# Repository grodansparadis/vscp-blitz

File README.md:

# Blitz
Wifi + Ethernet + CAN board for VSCP

<hr>

This project is part of the <a href="http://www.vscp.org">VSCP (Very Simple Control Protocol) project</a>. 

<hr>

This project is licensed under the 
<a href="http://creativecommons.org/licenses/by-nc-sa/3.0/">Creative Commons open source license Attribution-NonCommercial-ShareAlike 3.0 Unported</a>. 
Other license options are available by conacting <a href="malto:info@grodansparadis.com">Paradis of the Frog AB</a>

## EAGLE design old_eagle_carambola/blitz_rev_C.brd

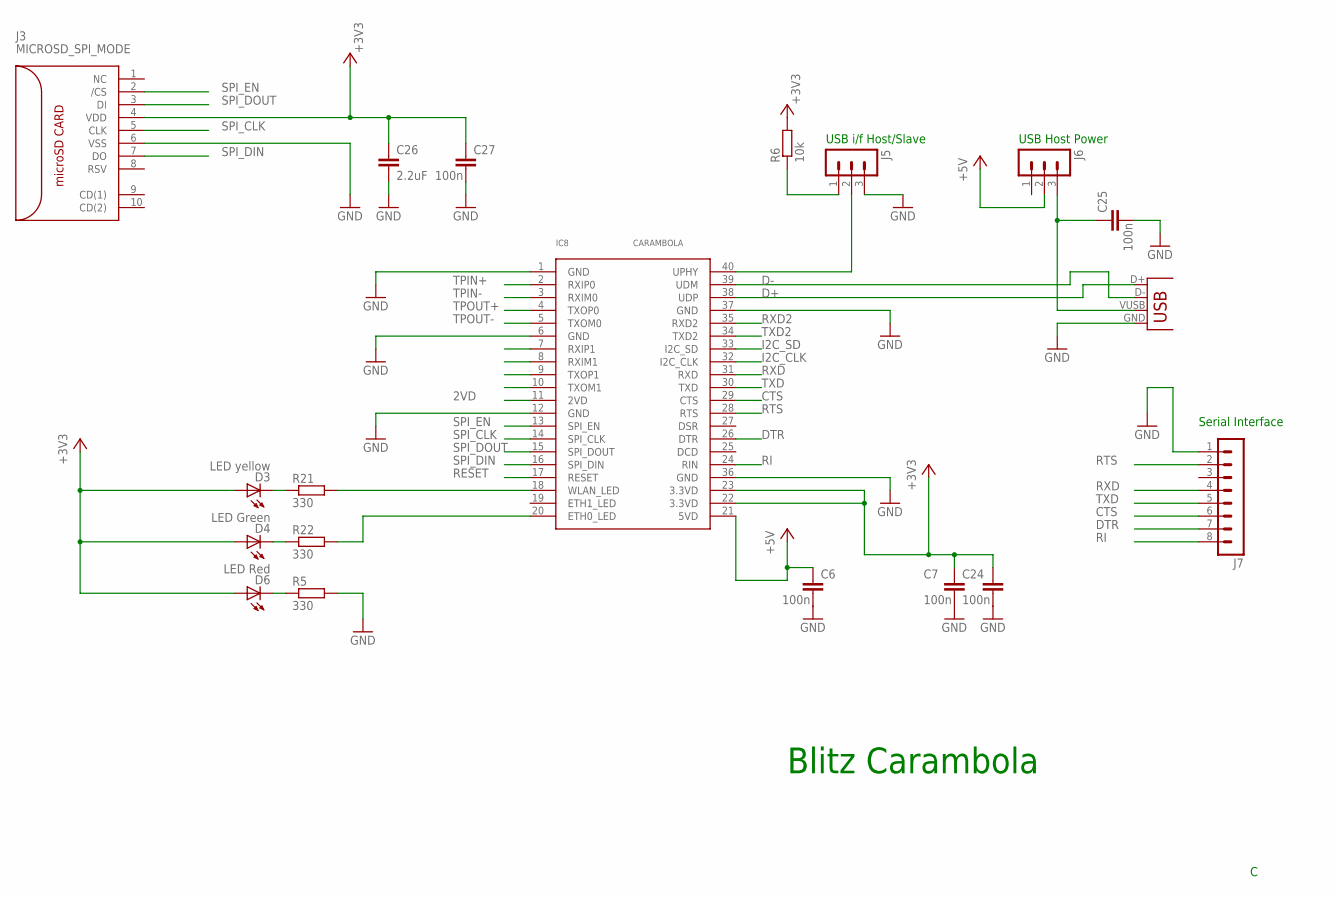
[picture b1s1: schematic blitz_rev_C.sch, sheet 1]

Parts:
C6, C7, C24, C25, C27: 100n; C0805
C26: 2.2uF; C2012
D3: LED yellow; C2012
D4: LED Green; C2012
D6: LED Red; C2012
IC8: CARAMBOLA
J3: MICROSD_SPI_MODE; MICRO_SD_CONNECTOR
J4: USB-B-S; USB-B-SMT
J5, J6: MA03-1
J7: MA08-1
R5, R21, R22: 330; M0805
R6: 10k; M0805

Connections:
2VD: IC8.11 (2VD)
+3V3: C7.1, C24.1, C26.1, C27.1, D3.1 (A), D4.1 (A), D6.1 (A), IC8.22 (3.3VD), IC8.23 (3.3VD), J3.4 (VDD), R6.2; also elsewhere on the board
+5V: C6.1, IC8.21 (5VD), J6.2; also elsewhere on the board
CTS: IC8.29 (CTS), J7.6
D+: IC8.38 (UDP), J4.D+
D-: IC8.39 (UDM), J4.D-
DTR: IC8.26 (DTR), J7.7
GND: C6.2, C7.2, C24.2, C25.2, C26.2, C27.2, IC8.1 (GND), IC8.6 (GND), IC8.12 (GND), IC8.36 (GND), IC8.37 (GND), J3.6 (VSS), J4.GND, J5.3, J7.1, R5.2; also elsewhere on the board
I2C_CLK: IC8.32 (I2C_CLK)
I2C_SD: IC8.33 (I2C_SD)
unnamed: J5.1, R6.1
unnamed: C25.1, J4.VUSB (VBUS), J6.3
unnamed: D4.2 (C), R22.1
unnamed: D3.2 (C), R21.1
unnamed: IC8.18 (WLAN_LED), R21.2
unnamed: IC8.20 (ETH0_LED), R22.2
unnamed: D6.2 (C), R5.1
unnamed: IC8.40 (UPHY), J5.2
RESET: IC8.17 (RESET)
RI: IC8.24 (RIN), J7.8
RTS: IC8.28 (RTS), J7.2
RXD: IC8.31 (RXD), J7.4
RXD2: IC8.35 (RXD2); also elsewhere on the board
SPI_CLK: IC8.14 (SPI_CLK), J3.5 (CLK)
SPI_DIN: IC8.16 (SPI_DIN), J3.7 (DO)
SPI_DOUT: IC8.15 (SPI_DOUT), J3.3 (DI)
SPI_EN: IC8.13 (SPI_EN), J3.2 (/CS)
TPIN+: IC8.2 (RXIP0); also elsewhere on the board
TPIN-: IC8.3 (RXIM0); also elsewhere on the board
TPOUT+: IC8.4 (TXOP0); also elsewhere on the board
TPOUT-: IC8.5 (TXOM0); also elsewhere on the board
TXD: IC8.30 (TXD), J7.5
TXD2: IC8.34 (TXD2); also elsewhere on the board

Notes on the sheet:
Blitz Carambola
USB i/f Host/Slave
USB Host Power
Serial Interface

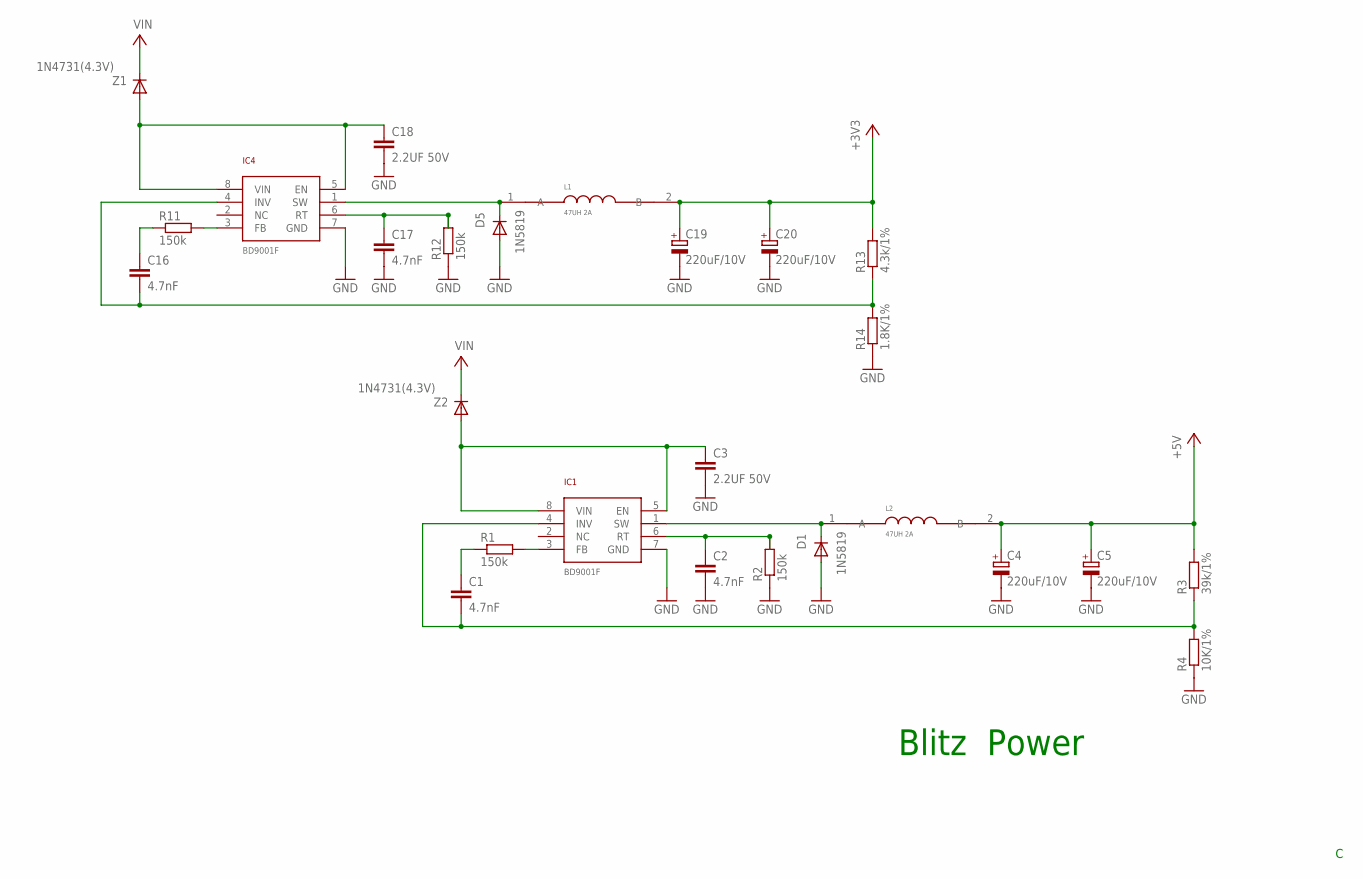
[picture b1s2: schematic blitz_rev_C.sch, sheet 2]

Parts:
C1, C2, C16, C17: 4.7nF; C0805
C3, C18: 2.2UF 50V; C2012
C4, C5, C19, C20: 220uF/10V; SMC_C
D1, D5: 1N5819; SOD-123
IC1, IC4: BD9001F; SOP8
L1, L2: 47UH 2A; NR10050T470M
R1, R2, R11, R12: 150k; M0805
R3: 39k/1%; M0805
R4: 10K/1%; M0805
R13: 4.3k/1%; M0805
R14: 1.8K/1%; M0805
Z1, Z2: 1N4731(4.3V); 1N4731

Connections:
+3V3: C19.+, C20.+, L1.2 (B), R13.2; also elsewhere on the board
+5V: C4.+, C5.+, L2.2 (B), R3.2; also elsewhere on the board
GND: C2.2, C3.2, C4.-, C5.-, C17.2, C18.2, C19.-, C20.-, D1.A, D5.A, IC1.7 (GND), IC4.7 (GND), R2.1, R4.1, R12.1, R14.1; also elsewhere on the board
unnamed: IC1.3 (FB), R1.2
unnamed: C1.1, R1.1
unnamed: C1.2, IC1.4 (INV), R3.1, R4.2
unnamed: C2.1, IC1.6 (RT), R2.2
unnamed: C3.1, IC1.5 (EN), IC1.8 (VIN), Z2.A
unnamed: D1.C, IC1.1 (SW), L2.1 (A)
unnamed: IC4.3 (FB), R11.2
unnamed: C16.1, R11.1
unnamed: C16.2, IC4.4 (INV), R13.1, R14.2
unnamed: C17.1, IC4.6 (RT), R12.2
unnamed: C18.1, IC4.5 (EN), IC4.8 (VIN), Z1.A
unnamed: D5.C, IC4.1 (SW), L1.1 (A)
V+: Z1.C, Z2.C; also elsewhere on the board

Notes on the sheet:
Blitz Power

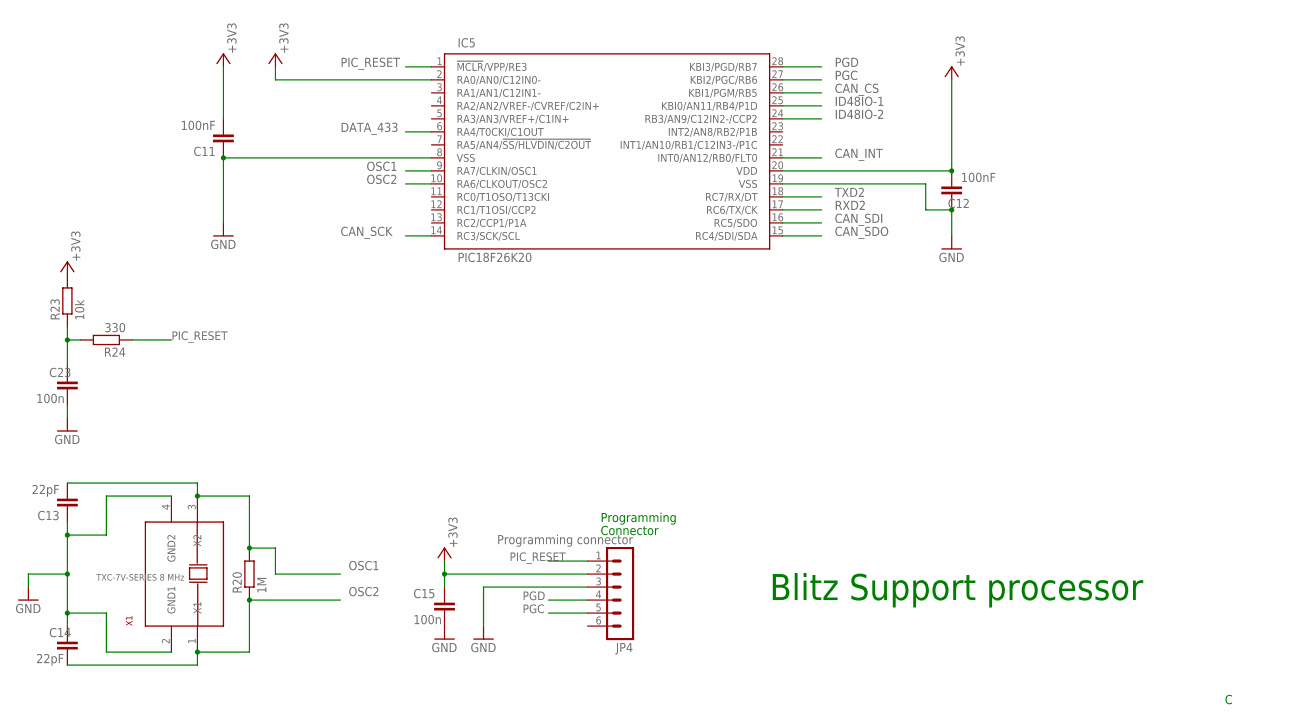
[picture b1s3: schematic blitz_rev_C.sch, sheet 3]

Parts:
C11, C12: 100nF; C0805
C13, C14: 22pF; C0805
C15, C23: 100n; C0805
IC5: PIC18F26K20; SSOP28
JP4: Programming connector; MA06-1
R20: 1M; M0805
R23: 10k; M0805
R24: 330; M0805
X1: TXC-7V-SERIES 8 MHz; TXC-7V-SERIES

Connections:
+3V3: C11.2, C12.2, C15.1, IC5.2 (RA0/AN0/C12IN0-), IC5.20 (VDD), JP4.2, R23.2; also elsewhere on the board
CAN_CS: IC5.26 (KBI1/PGM/RB5); also elsewhere on the board
CAN_INT: IC5.21 (INT0/AN12/RB0/FLT0); also elsewhere on the board
CAN_SCK: IC5.14 (RC3/SCK/SCL); also elsewhere on the board
CAN_SDI: IC5.16 (RC5/SDO); also elsewhere on the board
CAN_SDO: IC5.15 (RC4/SDI/SDA); also elsewhere on the board
DATA_433: IC5.6 (RA4/T0CKI/C1OUT); also elsewhere on the board
GND: C11.1, C12.1, C13.1, C14.1, C15.2, C23.2, IC5.8 (VSS), IC5.19 (VSS), JP4.3, X1.2 (GND1), X1.4 (GND2); also elsewhere on the board
ID48IO-1: IC5.25 (KBI0/AN11/RB4/P1D); also elsewhere on the board
ID48IO-2: IC5.24 (RB3/AN9/C12IN2-/CCP2); also elsewhere on the board
unnamed: C23.1, R23.1, R24.2
OSC1: C13.2, IC5.9 (RA7/CLKIN/OSC1), R20.2, X1.3 (X2)
OSC2: C14.2, IC5.10 (RA6/CLKOUT/OSC2), R20.1, X1.1 (X1)
PGC: IC5.27 (KBI2/PGC/RB6), JP4.5
PGD: IC5.28 (KBI3/PGD/RB7), JP4.4
PIC_RESET: IC5.1 (!MCLR!/VPP/RE3), JP4.1, R24.1
RXD2: IC5.17 (RC6/TX/CK); also elsewhere on the board
TXD2: IC5.18 (RC7/RX/DT); also elsewhere on the board

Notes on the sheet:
Programming
Connector
Blitz Support processor

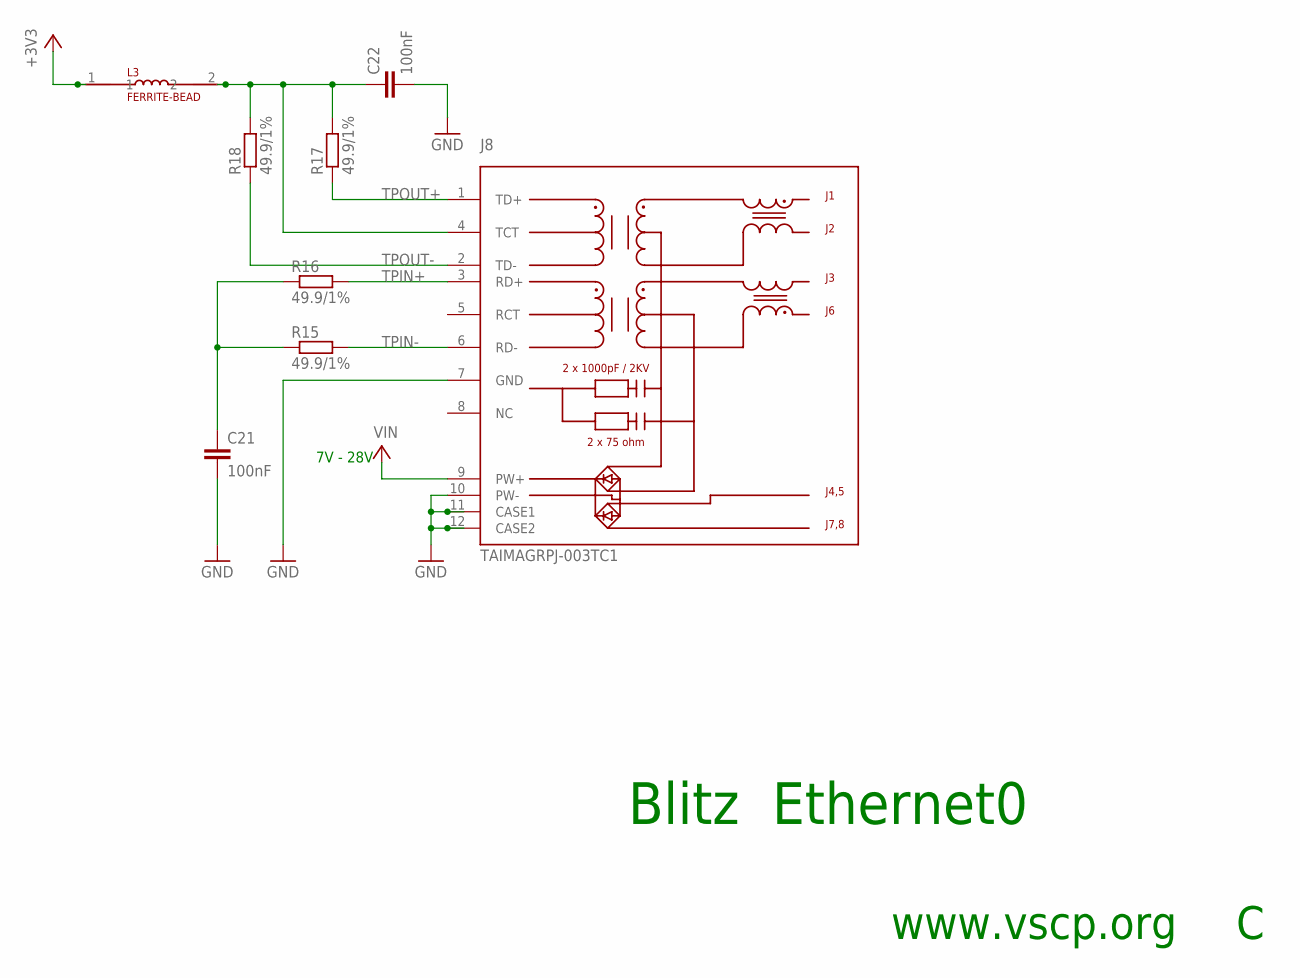
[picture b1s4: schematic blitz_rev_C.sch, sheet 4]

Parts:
C21, C22: 100nF; C0805
J8: TAIMAGRPJ-003TC1; TAIMAGRJP-003TC1
L3: FERRITE-BEAD; 0805
R15, R16, R17, R18: 49.9/1%; M0805

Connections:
+3V3: L3.1; also elsewhere on the board
GND: C21.2, C22.2, J8.7 (GND), J8.10 (PW-), J8.11 (CASE1), J8.12 (CASE2); also elsewhere on the board
unnamed: C21.1, R15.1, R16.1
unnamed: C22.1, J8.4 (TCT), L3.2, R17.2, R18.2
TPIN+: J8.3 (RD+), R16.2; also elsewhere on the board
TPIN-: J8.6 (RD-), R15.2; also elsewhere on the board
TPOUT+: J8.1 (TD+), R17.1; also elsewhere on the board
TPOUT-: J8.2 (TD-), R18.1; also elsewhere on the board
V+: J8.9 (PW+); also elsewhere on the board

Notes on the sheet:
Blitz Ethernet0
7V - 28V
www.vscp.org

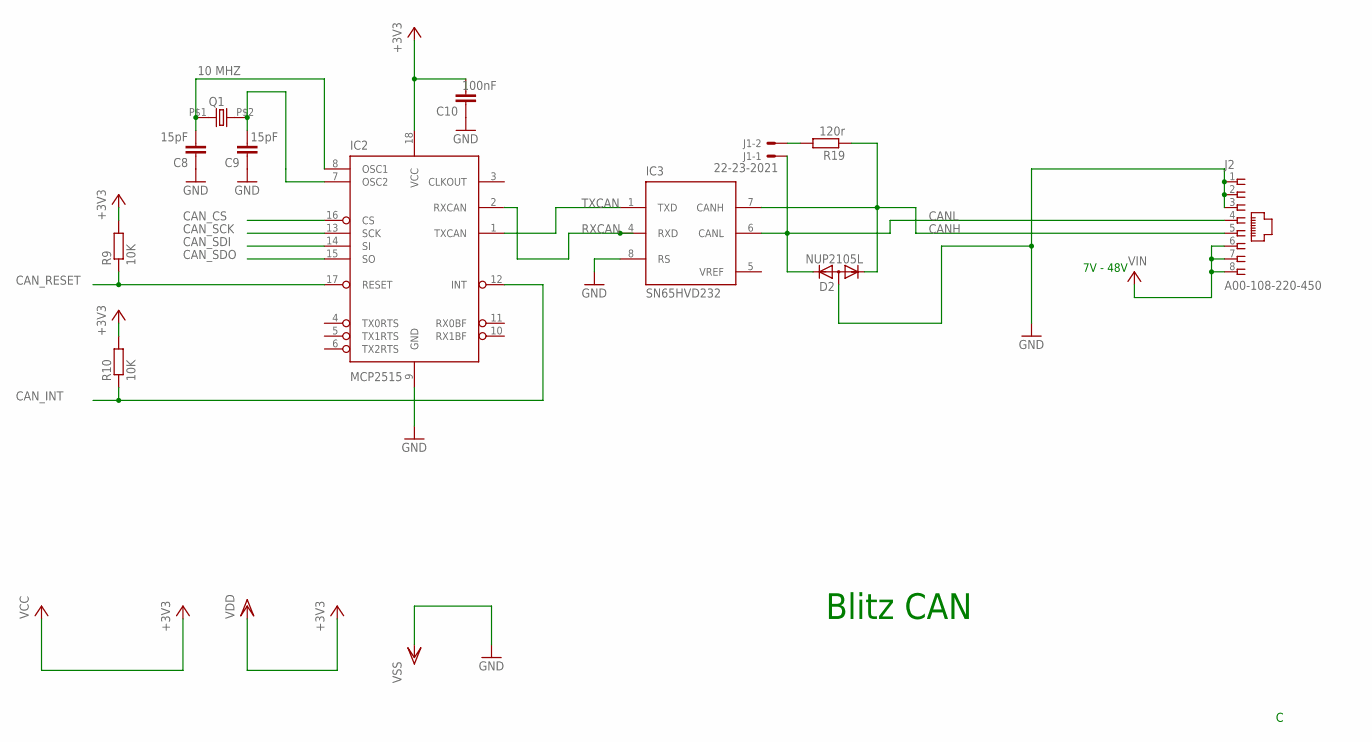
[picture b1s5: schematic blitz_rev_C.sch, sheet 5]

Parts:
C8, C9: 15pF; C0805
C10: 100nF; C0805
D2: NUP2105L; SOT23
IC2: MCP2515; SO-18W
IC3: SN65HVD232; SO-08
J1: 22-23-2021
J2: A00-108-220-450; RJ-45
Q1: 10 MHZ; 9C
R9, R10: 10K; R0805
R19: 120r; R0805

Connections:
+3V3: C10.2, IC2.18 (VCC), IC3.3 (VDD), R9.2, R10.2; also elsewhere on the board
CANH: D2.1 (K1), IC3.7 (CANH), J2.5, R19.1
CANL: D2.2 (K2), IC3.6 (CANL), J1.1, J2.4
CAN_CS: IC2.16 (CS); also elsewhere on the board
CAN_INT: IC2.12 (INT), R10.1; also elsewhere on the board
CAN_RESET: IC2.17 (RESET), R9.1
CAN_SCK: IC2.13 (SCK); also elsewhere on the board
CAN_SDI: IC2.14 (SI); also elsewhere on the board
CAN_SDO: IC2.15 (SO); also elsewhere on the board
GND: C8.1, C9.1, C10.1, D2.3 (A), IC2.9 (GND), IC3.2 (VSS), IC3.8 (RS), J2.1, J2.2, J2.3; also elsewhere on the board
unnamed: C8.2, IC2.8 (OSC1), Q1.P$1 (1)
unnamed: C9.2, IC2.7 (OSC2), Q1.P$2 (2)
unnamed: J1.2, R19.2
RXCAN: IC2.2 (RXCAN), IC3.4 (RXD)
TXCAN: IC2.1 (TXCAN), IC3.1 (TXD)
V+: J2.6, J2.7, J2.8; also elsewhere on the board
VREF: IC3.5 (VREF)

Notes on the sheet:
Blitz CAN
7V - 48V

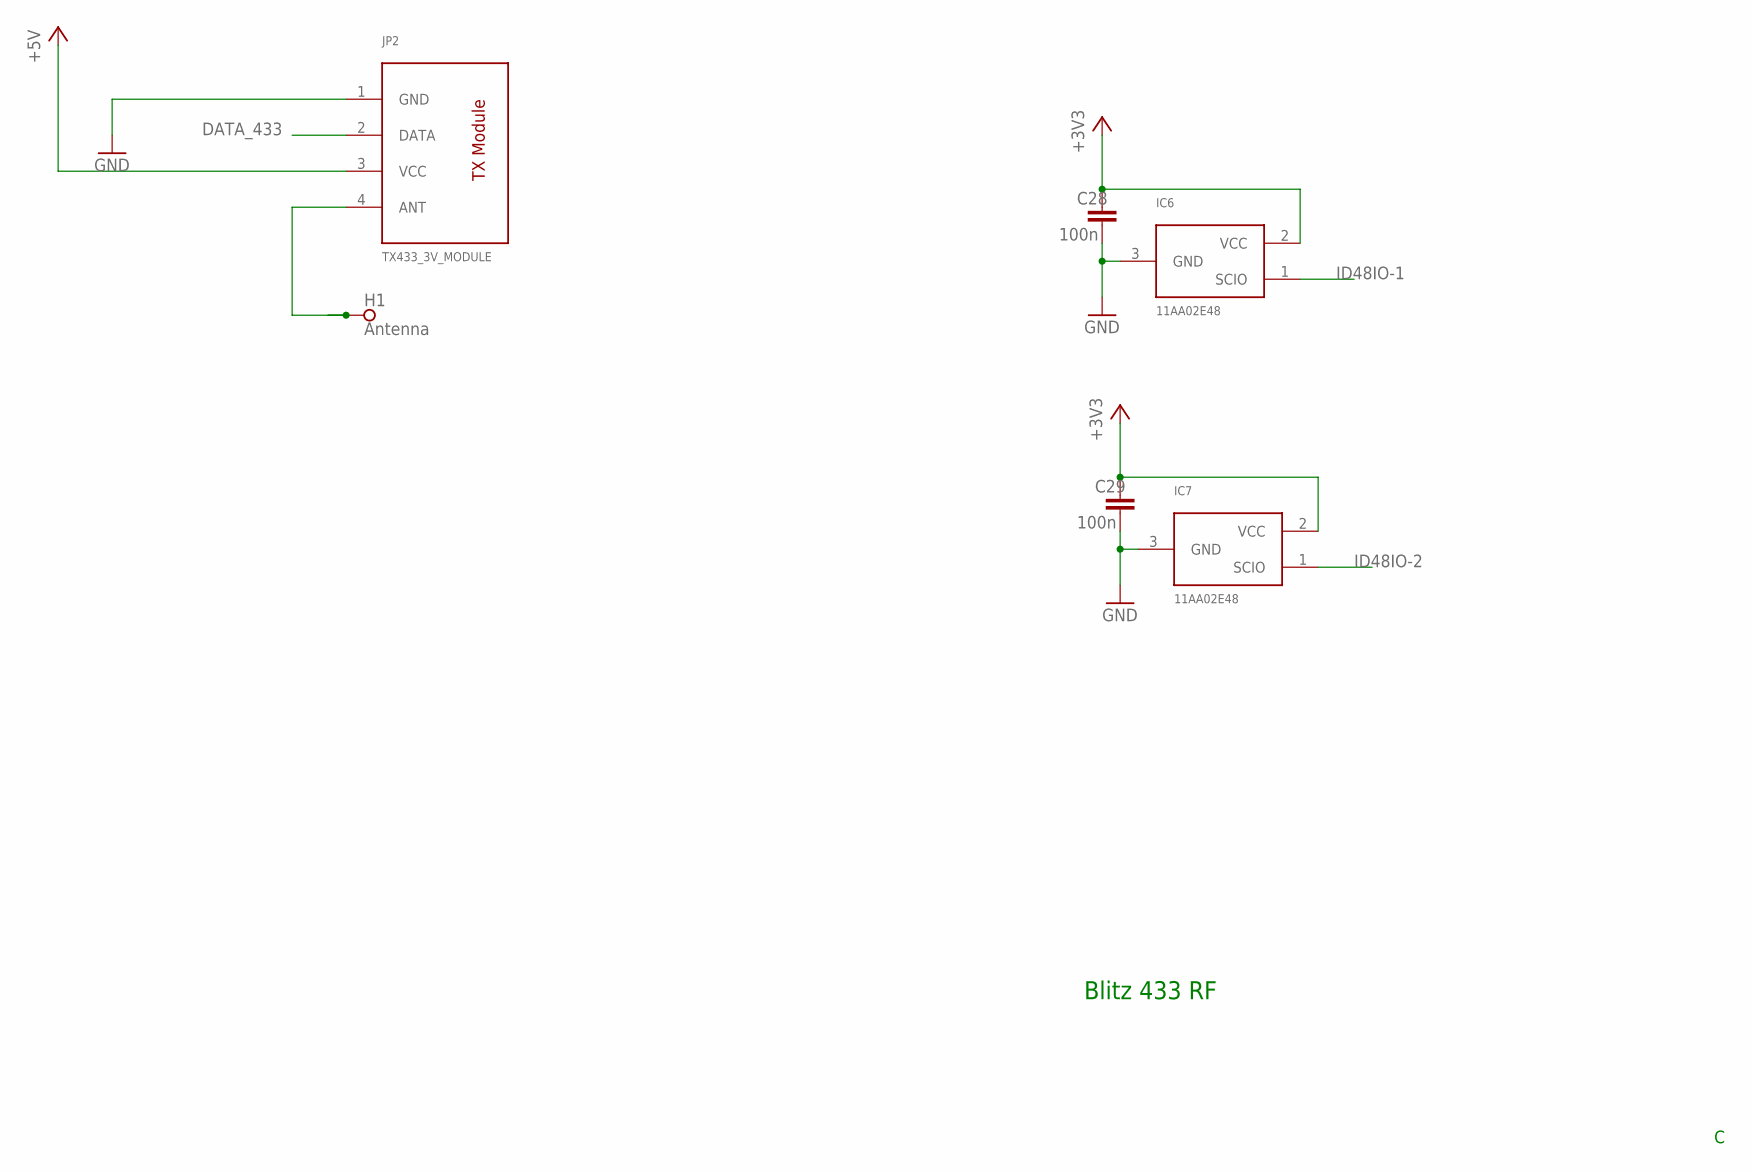
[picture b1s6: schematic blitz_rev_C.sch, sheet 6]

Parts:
C28, C29: 100n; C0805
H1: Antenna; PAD_0.1000
IC6, IC7: 11AA02E48; SOT23
JP2: TX433_3V_MODULE; FOUR

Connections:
+3V3: C28.1, C29.1, IC6.2 (VCC), IC7.2 (VCC); also elsewhere on the board
+5V: JP2.3 (VCC); also elsewhere on the board
ANT: H1.1, JP2.4 (ANT)
DATA_433: JP2.2 (DATA); also elsewhere on the board
GND: C28.2, C29.2, IC6.3 (GND), IC7.3 (GND), JP2.1 (GND); also elsewhere on the board
ID48IO-1: IC6.1 (SCIO); also elsewhere on the board
ID48IO-2: IC7.1 (SCIO); also elsewhere on the board

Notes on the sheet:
Blitz 433 RF

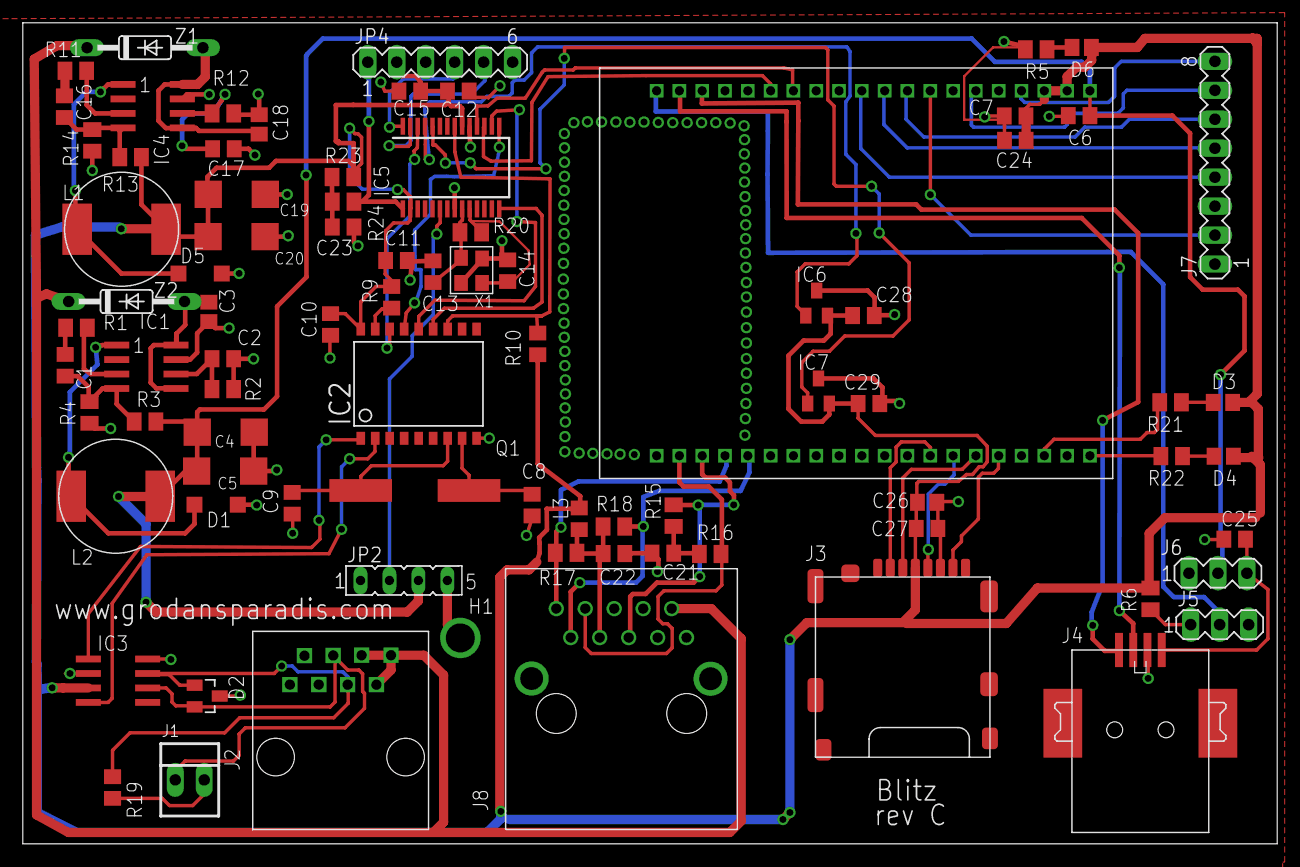
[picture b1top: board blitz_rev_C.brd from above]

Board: 2 copper layers, 110.0 x 72.0 mm, 83 parts (0 on the bottom side), 67 nets.

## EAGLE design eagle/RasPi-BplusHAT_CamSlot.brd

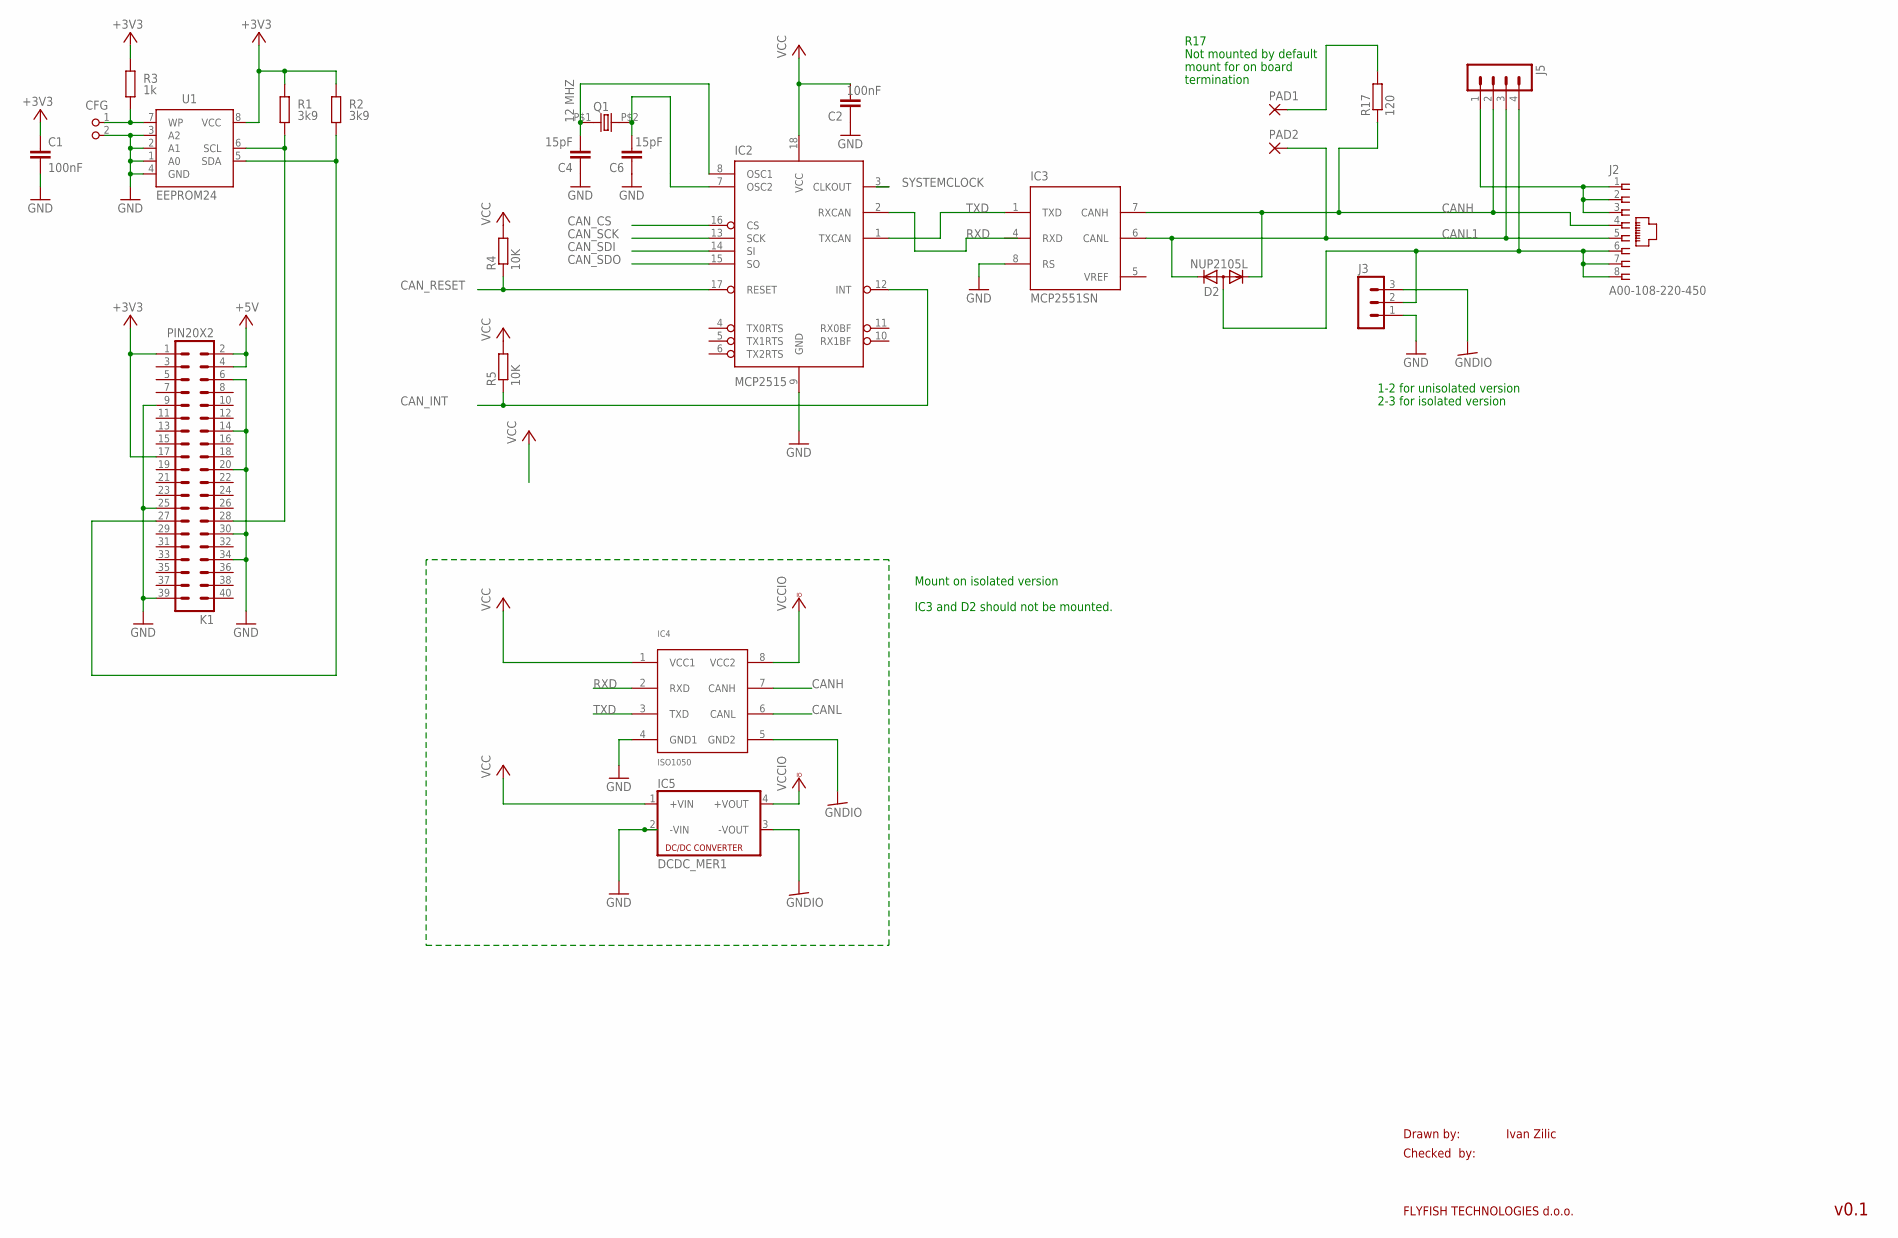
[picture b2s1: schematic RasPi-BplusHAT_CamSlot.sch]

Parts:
C1: 100nF; C0805K
C2: 100nF; C0805
C4, C6: 15pF; C0805
CFG: PIN2_100; PIN_W_2
D2: NUP2105L; SOT23
IC2: MCP2515; SO-18W
IC3: MCP2551SN; SO-08
IC4: ISO1050; DUB_PSOP
IC5: DCDC_MER1; MER1
J2: A00-108-220-450; RJ-45
J3: MA03-1
J5: MA04-1
K1: PIN20X2; PIN_20X2
PAD1, PAD2: 1,6/0,8
Q1: 12 MHZ; 9C
R1, R2: 3k9; M0805; TOLERANCE 5%
R3: 1k; M0805; TOLERANCE 5%
R4, R5: 10K; R0805
R17: 120; R0805
U1: EEPROM24; SOIC8

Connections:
+3V3: C1.1, K1.1, K1.17, R1.2, R2.2, R3.2, U1.8 (VCC)
+5V: K1.2, K1.4
CANH: D2.1 (K1), IC3.7 (CANH), IC4.7 (CANH), J2.4, J5.2, R17.1
CANL: IC4.6 (CANL)
CANL1: D2.2 (K2), IC3.6 (CANL), J2.5, J5.3, PAD2.1
CAN_CS: IC2.16 (CS)
CAN_INT: IC2.12 (INT), R5.1
CAN_RESET: IC2.17 (RESET), R4.1
CAN_SCK: IC2.13 (SCK)
CAN_SDI: IC2.14 (SI)
CAN_SDO: IC2.15 (SO)
GND: C1.2, C2.1, C4.1, C6.1, CFG.2, IC2.9 (GND), IC3.8 (RS), IC4.4 (GND1), IC5.2 (-VIN), J3.1, K1.6, K1.9, K1.14, K1.20, K1.25, K1.30, K1.34, K1.39, U1.1 (A0), U1.2 (A1), U1.3 (A2), U1.4 (GND)
GNDIO: IC4.5 (GND2), IC5.3 (-VOUT), J3.3
unnamed: K1.28, R1.1, U1.6 (SCL)
unnamed: K1.27, R2.1, U1.5 (SDA)
unnamed: CFG.1, R3.1, U1.7 (WP)
unnamed: C4.2, IC2.8 (OSC1), Q1.P$1 (1)
unnamed: C6.2, IC2.7 (OSC2), Q1.P$2 (2)
unnamed: D2.3 (A), J2.6, J2.7, J2.8, J3.2, J5.4
unnamed: PAD1.1, R17.2
unnamed: J2.1, J2.2, J2.3, J5.1
RXD: IC2.2 (RXCAN), IC4.2 (RXD)
SYSTEMCLOCK: IC2.3 (CLKOUT)
TXD: IC2.1 (TXCAN), IC3.1 (TXD), IC4.3 (TXD)
VCC: C2.2, IC2.18 (VCC), IC4.1 (VCC1), IC5.1 (+VIN), R4.2, R5.2
VCCIO: IC4.8 (VCC2), IC5.4 (+VOUT)
VDD: IC3.3 (VDD)
VREF: IC3.5 (VREF)
VSS: IC3.2 (VSS)

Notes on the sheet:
Drawn by:
Checked by:
FLYFISH TECHNOLOGIES d.o.o.
Ivan Zilic
v0.1
1-2 for unisolated version
2-3 for isolated version
Not mounted by default
mount for on board
termination
R17
Mount on isolated version
IC3 and D2 should not be mounted.

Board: 2 copper layers, 24 parts (0 on the bottom side), 20 nets, no tracks yet.

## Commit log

2015-08-28 Move from private to public
2015-12-17 Updated readme and license
2018-05-22 Make in sync
